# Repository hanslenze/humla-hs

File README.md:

# Humla-HS (with Choc hotswap sockets)
Because I find myself wanting to experiment with different types of Choc v1 switches, I've modified the original [Humla keyboard](https://github.com/jimmerricks/humla) with Choc v1 hotswap sockets.

##Original text:
The Humla is a 36-key low profile keyboard based on [the Reviung by gtips](https://github.com/gtips/reviung/) and [the Rev-lp by cyril279](https://github.com/cyril279/keyboards/tree/main/revlp). It is for choc switches (with 18x17mm spacing) and has basic support for bluetooth pro micro alternatives such as the [nRFMicro](https://github.com/joric/nrfmicro). Humla means blumblebee in Swedish.

## 3D printed cases

- Basic [case](./case) with cover by [@zzeneg](https://github.com/zzeneg)
- Laptop [adapter](https://github.com/Lenbok/scad-keyboard-cases/tree/master/humla) and bumper by [@Lenbok](https://github.com/Lenbok)

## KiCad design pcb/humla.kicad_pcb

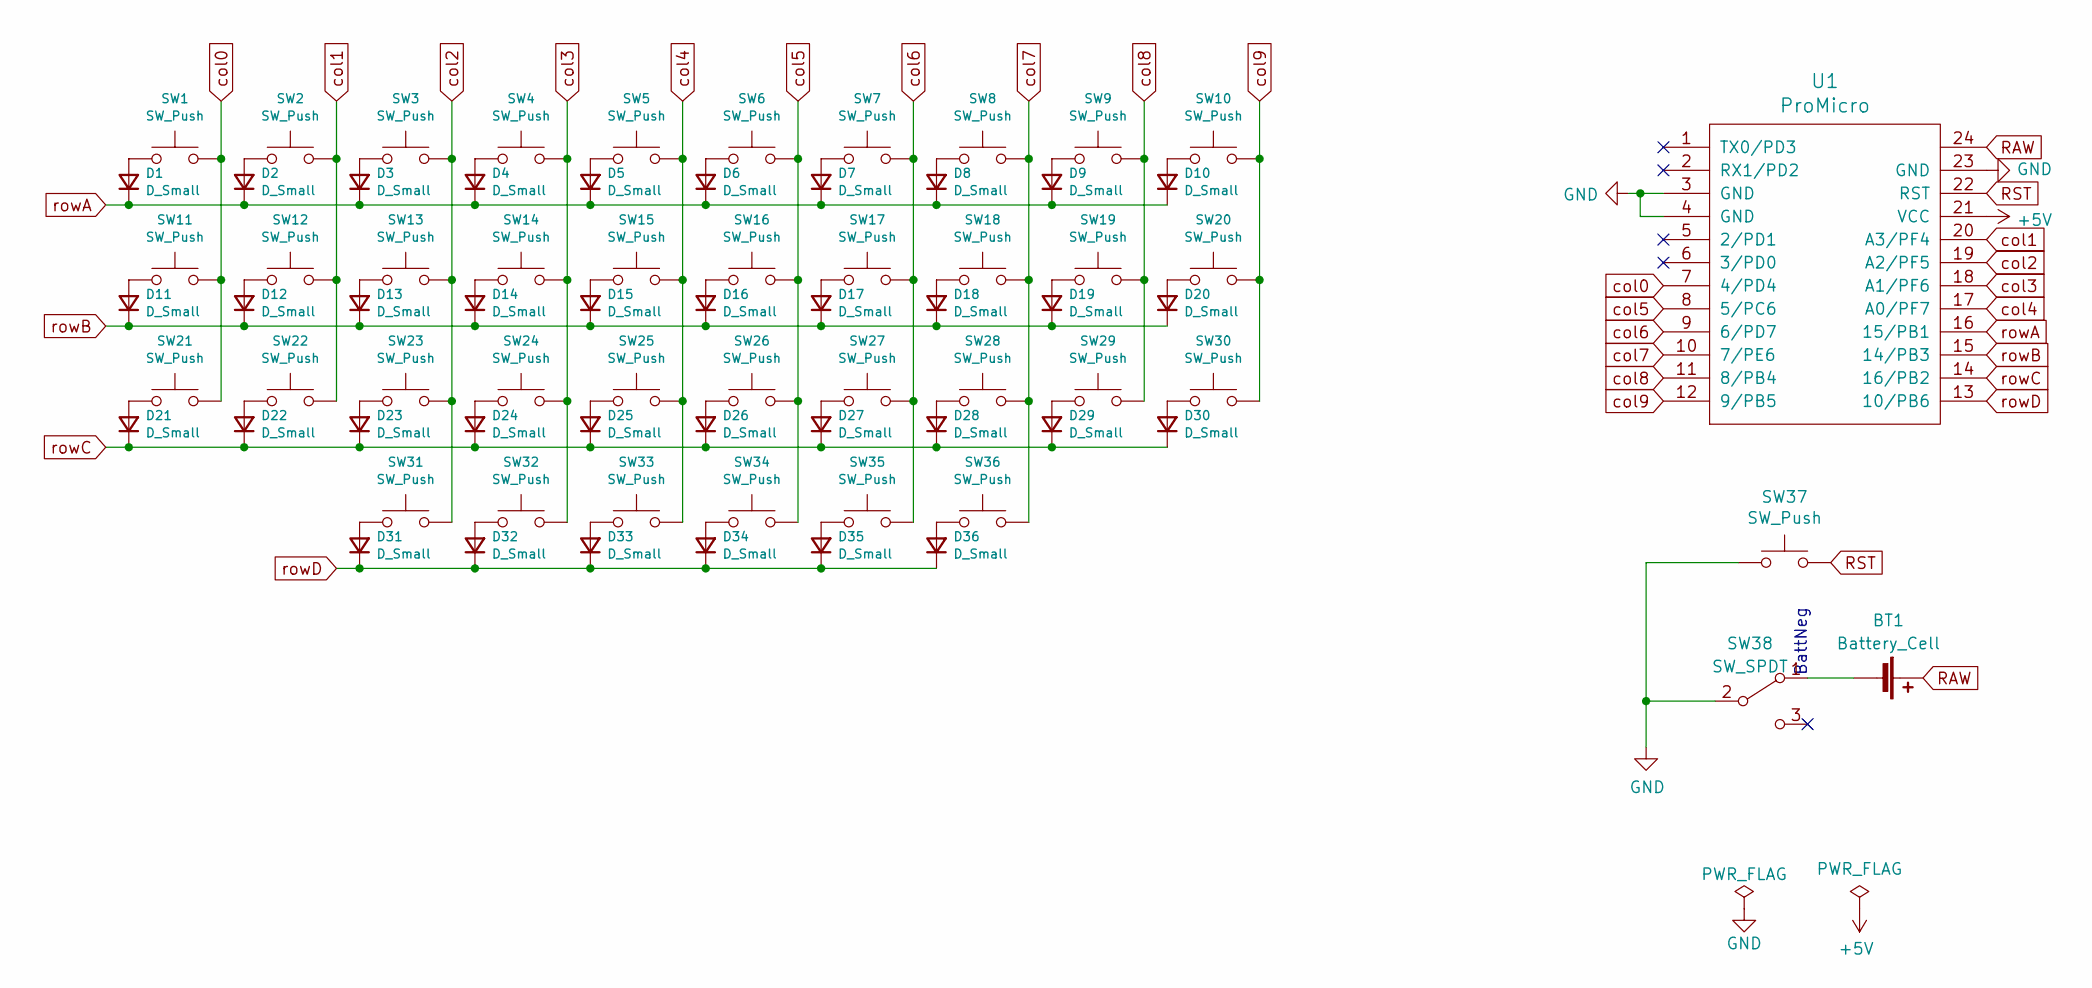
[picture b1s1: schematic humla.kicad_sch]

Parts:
BT1: Battery_Cell; Battery_pads
D1, D2, D3, D4, D5, D6, D7, D8, D9, D10, D11, D12, D13, D14, D15, D16, D17, D18, D19, D20, D21, D22, D23, D24, D25, D26, D27, D28, D29, D30, D31, D32, D33, D34, D35, D36: D_Small; D3_SMD
SW1, SW2, SW3, SW4, SW5, SW6, SW7, SW8, SW9, SW10, SW11, SW12, SW13, SW14, SW15, SW16, SW17, SW18, SW19, SW20, SW21, SW22, SW23, SW24, SW25, SW26, SW27, SW28, SW29, SW30, SW31, SW32, SW33, SW34, SW35, SW36: SW_Push; Kailh_socket_PG1350_optional
SW37: SW_Push; Reset
SW38: SW_SPDT; power_switch
U1: ProMicro; ArduinoProMicro

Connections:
+5V: U1.21 (VCC)
GND: SW37.1, SW38.2 (B), U1.3 (GND), U1.4 (GND), U1.23 (GND)
unnamed: BT1.2 (-), SW38.1 (A)
unnamed: D1.2 (A), SW1.1
unnamed: D2.2 (A), SW2.1
unnamed: D3.2 (A), SW3.1
unnamed: D4.2 (A), SW4.1
unnamed: D5.2 (A), SW5.1
unnamed: D6.2 (A), SW6.1
unnamed: D7.2 (A), SW7.1
unnamed: D8.2 (A), SW8.1
unnamed: D9.2 (A), SW9.1
unnamed: D10.2 (A), SW10.1
unnamed: D11.2 (A), SW11.1
unnamed: D12.2 (A), SW12.1
unnamed: D13.2 (A), SW13.1
unnamed: D14.2 (A), SW14.1
unnamed: D15.2 (A), SW15.1
unnamed: D16.2 (A), SW16.1
unnamed: D17.2 (A), SW17.1
unnamed: D18.2 (A), SW18.1
unnamed: D19.2 (A), SW19.1
unnamed: D20.2 (A), SW20.1
unnamed: D21.2 (A), SW21.1
unnamed: D22.2 (A), SW22.1
unnamed: D23.2 (A), SW23.1
unnamed: D24.2 (A), SW24.1
unnamed: D25.2 (A), SW25.1
unnamed: D26.2 (A), SW26.1
unnamed: D27.2 (A), SW27.1
unnamed: D28.2 (A), SW28.1
unnamed: D29.2 (A), SW29.1
unnamed: D30.2 (A), SW30.1
unnamed: D31.2 (A), SW31.1
unnamed: D32.2 (A), SW32.1
unnamed: D33.2 (A), SW33.1
unnamed: D34.2 (A), SW34.1
unnamed: D35.2 (A), SW35.1
unnamed: D36.2 (A), SW36.1
RAW: BT1.1 (+), U1.24
RST: SW37.2, U1.22 (RST)
col0: SW1.2, SW11.2, SW21.2, U1.7 (4/PD4)
col1: SW2.2, SW12.2, SW22.2, U1.20 (A3/PF4)
col2: SW3.2, SW13.2, SW23.2, SW31.2, U1.19 (A2/PF5)
col3: SW4.2, SW14.2, SW24.2, SW32.2, U1.18 (A1/PF6)
col4: SW5.2, SW15.2, SW25.2, SW33.2, U1.17 (A0/PF7)
col5: SW6.2, SW16.2, SW26.2, SW34.2, U1.8 (5/PC6)
col6: SW7.2, SW17.2, SW27.2, SW35.2, U1.9 (6/PD7)
col7: SW8.2, SW18.2, SW28.2, SW36.2, U1.10 (7/PE6)
col8: SW9.2, SW19.2, SW29.2, U1.11 (8/PB4)
col9: SW10.2, SW20.2, SW30.2, U1.12 (9/PB5)
rowA: D1.1 (K), D2.1 (K), D3.1 (K), D4.1 (K), D5.1 (K), D6.1 (K), D7.1 (K), D8.1 (K), D9.1 (K), D10.1 (K), U1.16 (15/PB1)
rowB: D11.1 (K), D12.1 (K), D13.1 (K), D14.1 (K), D15.1 (K), D16.1 (K), D17.1 (K), D18.1 (K), D19.1 (K), D20.1 (K), U1.15 (14/PB3)
rowC: D21.1 (K), D22.1 (K), D23.1 (K), D24.1 (K), D25.1 (K), D26.1 (K), D27.1 (K), D28.1 (K), D29.1 (K), D30.1 (K), U1.14 (16/PB2)
rowD: D31.1 (K), D32.1 (K), D33.1 (K), D34.1 (K), D35.1 (K), D36.1 (K), U1.13 (10/PB6)

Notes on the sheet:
BattNeg

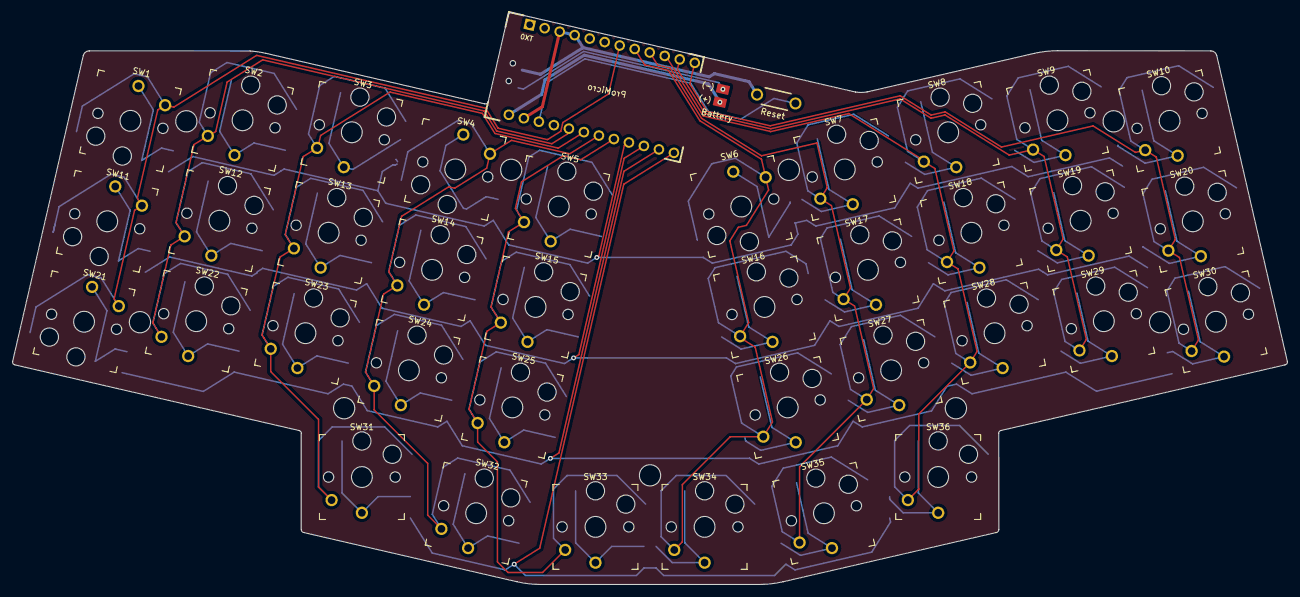
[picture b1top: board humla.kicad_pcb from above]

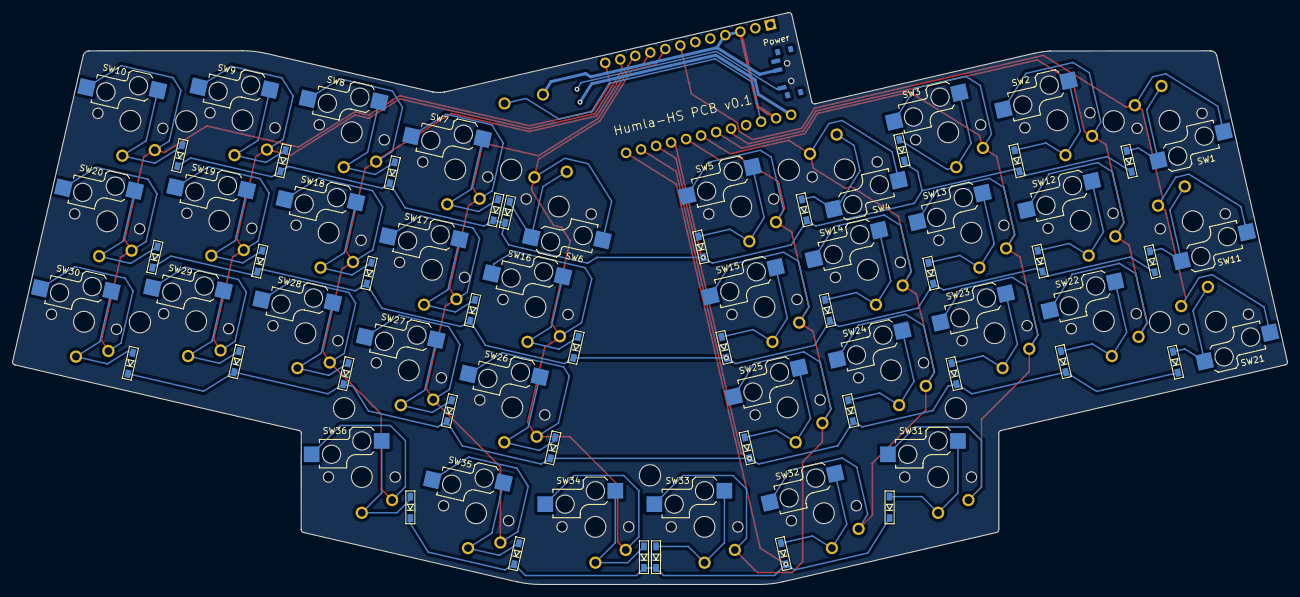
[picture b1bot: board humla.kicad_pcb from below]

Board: 2 copper layers, 210.2 x 94.3 mm, 85 parts (38 on the bottom side), 54 nets.

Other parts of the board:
h2, h2#2, h2#3, h2#4, h2#5, h2#6, h2#7, h2#8, h2#9: h2; M2_hole_3.5mm

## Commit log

2024-06-24 Sharing is caring
